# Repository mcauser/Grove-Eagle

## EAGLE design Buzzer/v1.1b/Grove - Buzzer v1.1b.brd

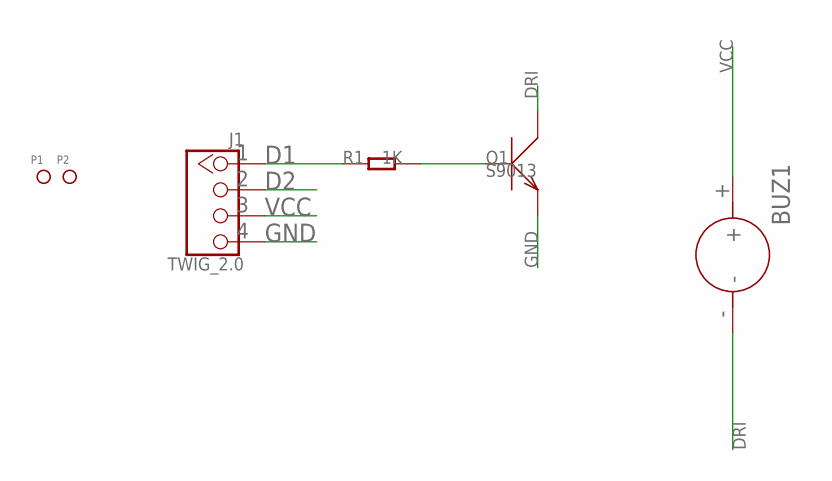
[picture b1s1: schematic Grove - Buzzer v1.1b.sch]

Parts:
BUZ1: BUZZER-YMD12065; 2P-7.6-D12X6.5H
J1: TWIG_2.0; 2.0_1X4
P1, P2: PAD-MARK; ROUND-MARK-1.0
Q1: S9013; SOT23
R1: 1K; R0603

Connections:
D1: J1.1, R1.1
D2: J1.2
DRI: BUZ1.-, Q1.3 (C)
GND: J1.4, Q1.2 (E)
unnamed: Q1.1 (B), R1.2
VCC: BUZ1.+, J1.3

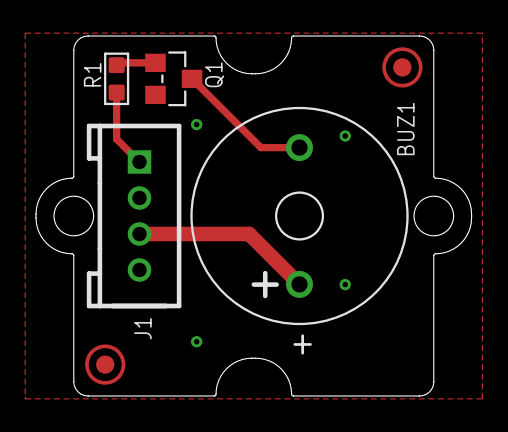
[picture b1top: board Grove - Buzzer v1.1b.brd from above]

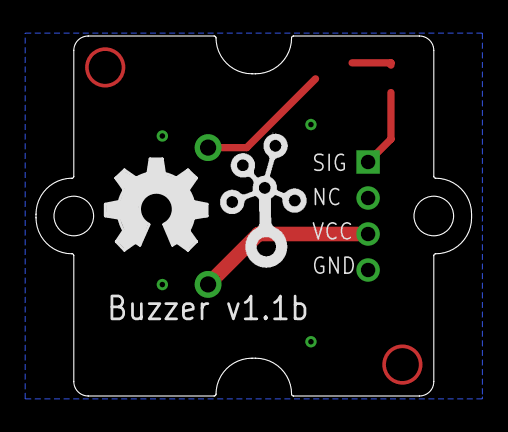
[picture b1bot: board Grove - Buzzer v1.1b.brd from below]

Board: 2 copper layers, 24.2 x 20.0 mm, 9 parts (2 on the bottom side), 5 nets.

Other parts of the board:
U$1: 1U-DIM-W/-DRILL
U$2: OSHW_FILLX200_NOTEXT
U$3: TWIGLOGO

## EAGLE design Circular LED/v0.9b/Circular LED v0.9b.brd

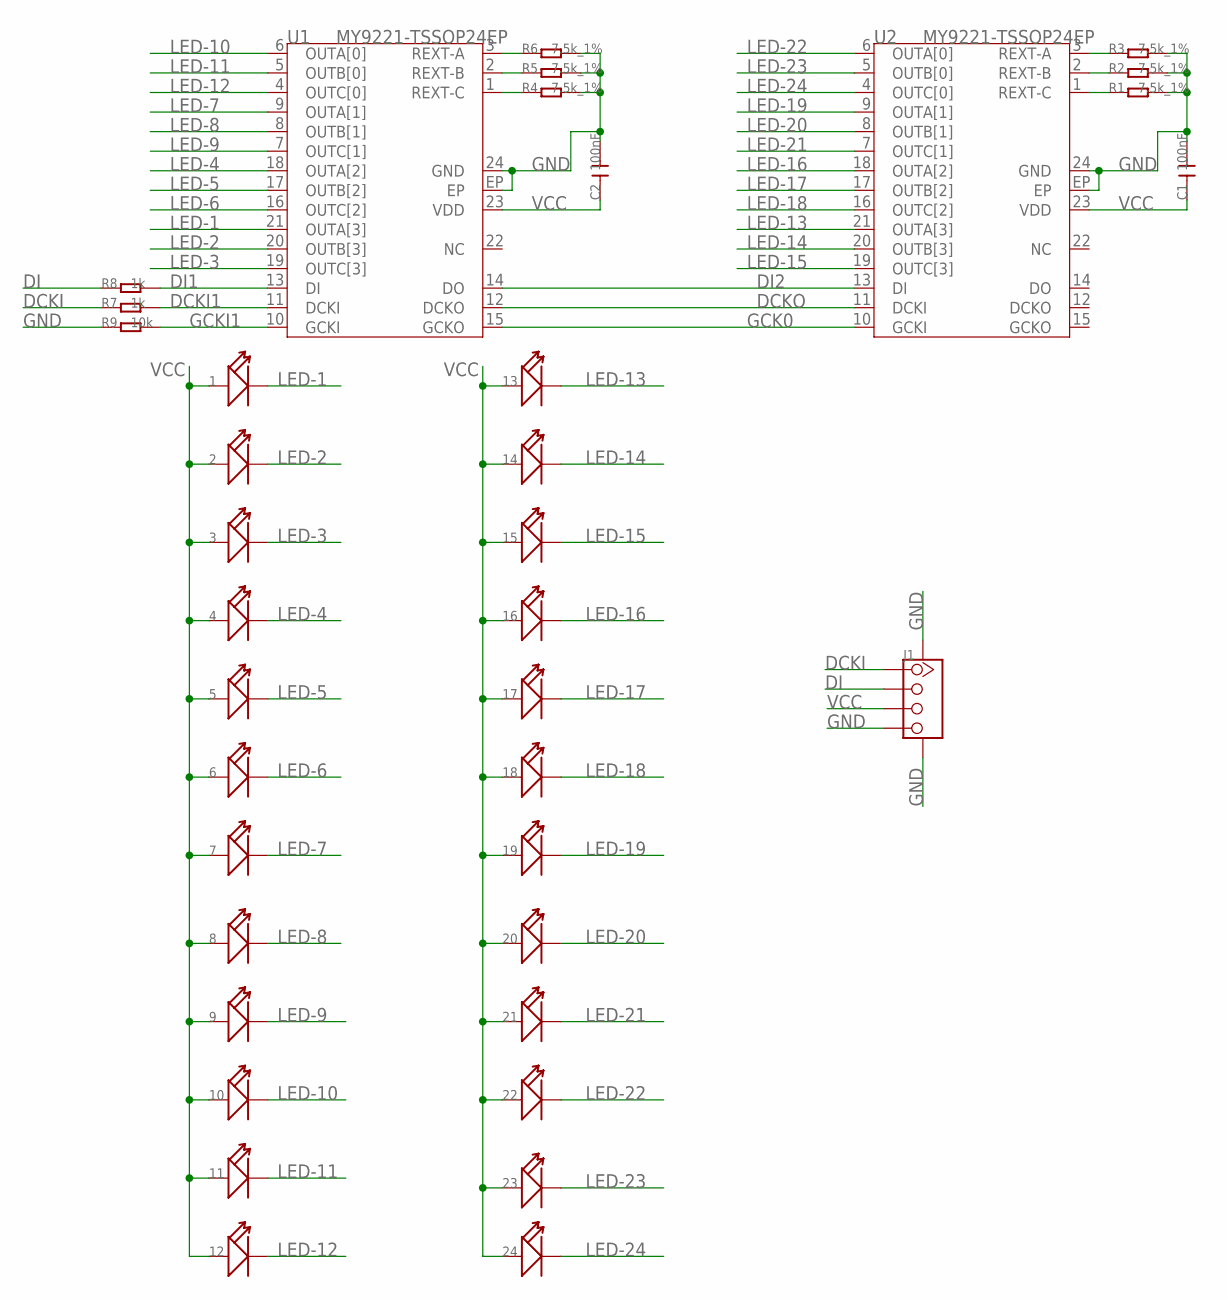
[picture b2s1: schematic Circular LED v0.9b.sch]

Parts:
1, 2, 3, 4, 5, 6, 7, 8, 9, 10, 11, 12, 13, 14, 15, 16, 17, 18, 19, 20, 21, 22, 23, 24: LED'1206'; LED-1206
C1, C2: 100nF; C0603
J1: TWIG-4P-2.0-SMD-FEMALE-REINFORCE'90D'; 4P-SMD-2.0-90D
R1, R2, R3, R4, R5, R6: 7.5k_1%; R0603
R7, R8: 1k; R0603
R9: 10k; R0603
U1, U2: MY9221-TSSOP24EP; TSSOP24EP

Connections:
DCKI: J1.1, R7.1
DCKI1: R7.2, U1.11 (DCKI)
DCKO: U1.12 (DCKO), U2.11 (DCKI)
DI: J1.2, R8.1
DI1: R8.2, U1.13 (DI)
DI2: U1.14 (DO), U2.13 (DI)
GCK0: U1.15 (GCKO), U2.10 (GCKI)
GCKI1: R9.2, U1.10 (GCKI)
GND: C1.2, C2.2, J1.4, J1.SS1, J1.SS2, R1.2, R2.2, R3.2, R4.2, R5.2, R6.2, R9.1, U1.24 (GND), U1.EP, U2.24 (GND), U2.EP
LED-1: 1.-, U1.21 (OUTA[3])
LED-2: 2.-, U1.20 (OUTB[3])
LED-3: 3.-, U1.19 (OUTC[3])
LED-4: 4.-, U1.18 (OUTA[2])
LED-5: 5.-, U1.17 (OUTB[2])
LED-6: 6.-, U1.16 (OUTC[2])
LED-7: 7.-, U1.9 (OUTA[1])
LED-8: 8.-, U1.8 (OUTB[1])
LED-9: 9.-, U1.7 (OUTC[1])
LED-10: 10.-, U1.6 (OUTA[0])
LED-11: 11.-, U1.5 (OUTB[0])
LED-12: 12.-, U1.4 (OUTC[0])
LED-13: 13.-, U2.21 (OUTA[3])
LED-14: 14.-, U2.20 (OUTB[3])
LED-15: 15.-, U2.19 (OUTC[3])
LED-16: 16.-, U2.18 (OUTA[2])
LED-17: 17.-, U2.17 (OUTB[2])
LED-18: 18.-, U2.16 (OUTC[2])
LED-19: 19.-, U2.9 (OUTA[1])
LED-20: 20.-, U2.8 (OUTB[1])
LED-21: 21.-, U2.7 (OUTC[1])
LED-22: 22.-, U2.6 (OUTA[0])
LED-23: 23.-, U2.5 (OUTB[0])
LED-24: 24.-, U2.4 (OUTC[0])
unnamed: R1.1, U2.1 (REXT-C)
unnamed: R2.1, U2.2 (REXT-B)
unnamed: R4.1, U1.1 (REXT-C)
unnamed: R5.1, U1.2 (REXT-B)
unnamed: R6.1, U1.3 (REXT-A)
unnamed: R3.1, U2.3 (REXT-A)
VCC: 1.+, 2.+, 3.+, 4.+, 5.+, 6.+, 7.+, 8.+, 9.+, 10.+, 11.+, 12.+, 13.+, 14.+, 15.+, 16.+, 17.+, 18.+, 19.+, 20.+, 21.+, 22.+, 23.+, 24.+, C1.1, C2.1, J1.3, U1.23 (VDD), U2.23 (VDD)

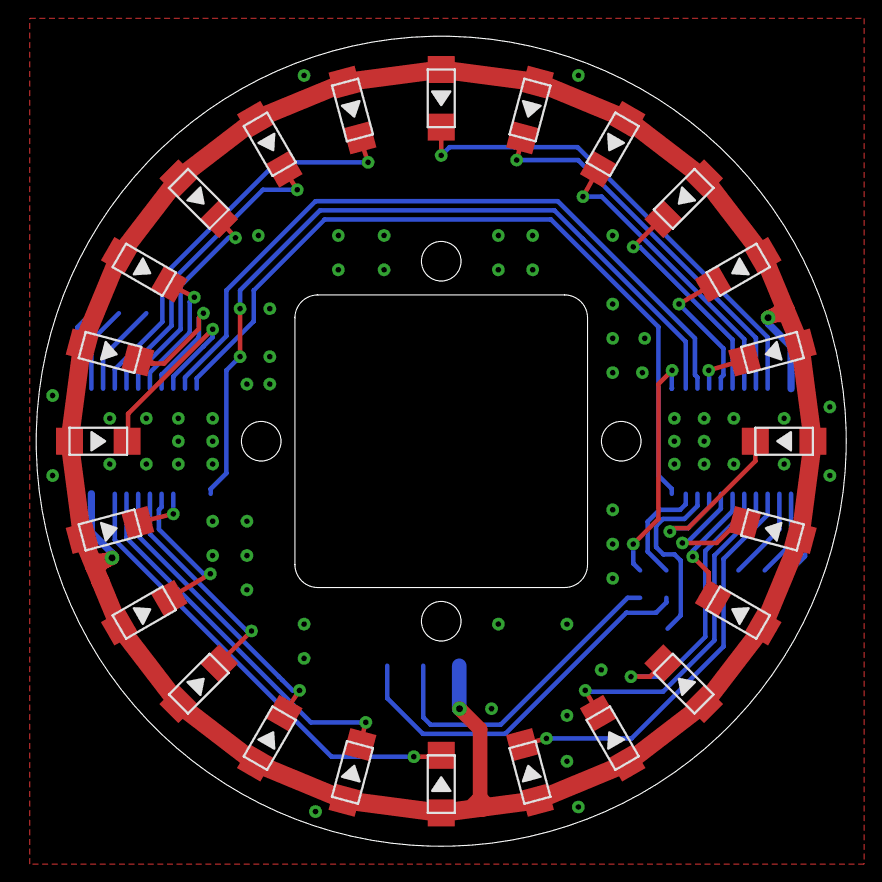
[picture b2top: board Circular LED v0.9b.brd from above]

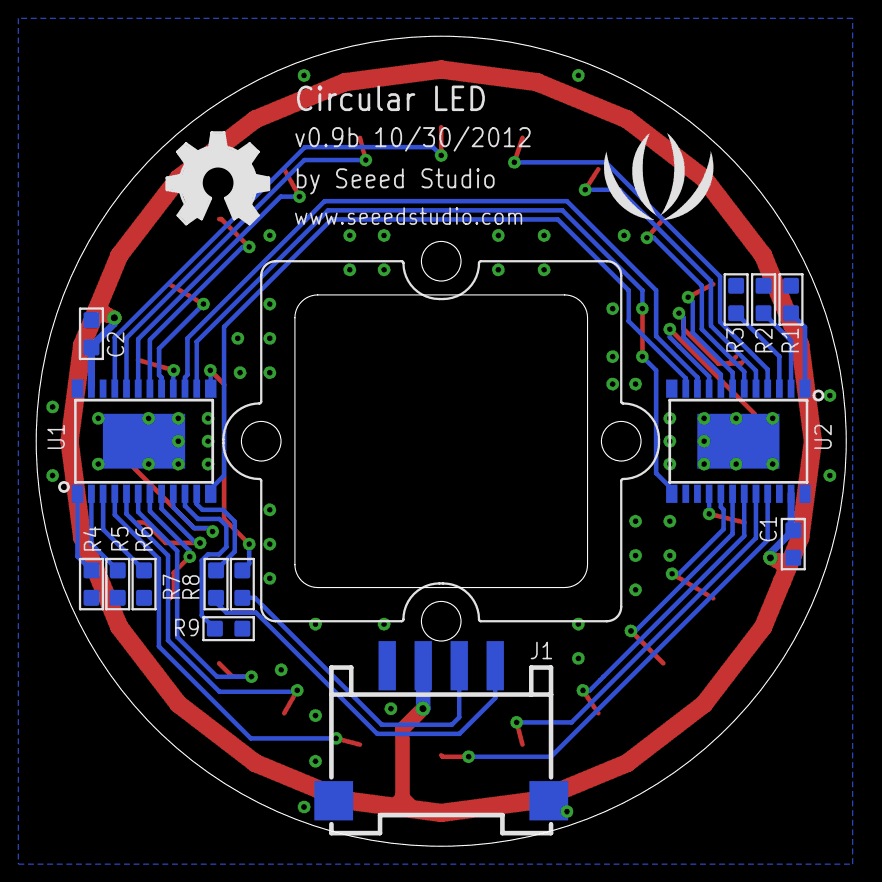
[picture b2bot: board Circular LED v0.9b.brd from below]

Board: 2 copper layers, 45.0 x 45.0 mm, 41 parts (17 on the bottom side), 40 nets.

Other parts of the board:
U$2: 1U-DIM-W/-DRILL-SILK
U$3: LOGO_SILK
U$4: OSHW_FILLX200_NOTEXT

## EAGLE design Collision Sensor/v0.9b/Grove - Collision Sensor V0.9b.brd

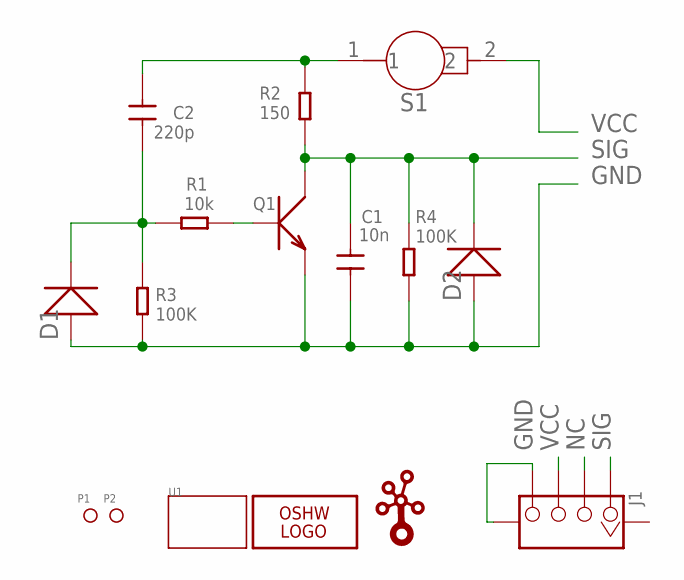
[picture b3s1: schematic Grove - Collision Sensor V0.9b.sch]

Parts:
C1: 10n; 0603
C2: 220p; 0603
D1, D2: D1N4148-SMD; DO-35-SMD
J1: TWIG-4P-2.0-SMD-FEMALE-REINFORCE'DD'; 4P-SMD-2.0
LOGO1: LOGO-OSHW-6MILX0200-NT; OSHW_6X200_NOTEXT
P1, P2: PAD-MARK; ROUND-MARK-0.635
Q1: TRANSISTOR-NPN-SOT23''; SOT23
R1: 10k; 0603
R2: 150; 0603
R3, R4: 100K; 0603
S1: SENSOR-COLLISION; 2P-ROUND-D5.4MM
U1: TWIG-1U; 1U-DIM-W/-DRILL
U$2: LOGO-TWIG; TWIGLOGO

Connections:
GND: C1.1, D1.A (+), D2.A (+), J1.4, J1.SS2, Q1.2 (E), R3.2, R4.2
unnamed: C2.2, R2.1, S1.1
unnamed: C2.1, D1.C (-), R1.2, R3.1
unnamed: Q1.1 (B), R1.1
NC: J1.2
SIG: C1.2, D2.C (-), J1.1, Q1.3 (C), R2.2, R4.1
VCC: J1.3, S1.2

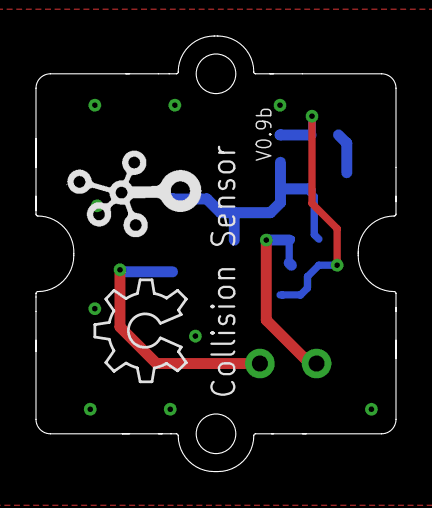
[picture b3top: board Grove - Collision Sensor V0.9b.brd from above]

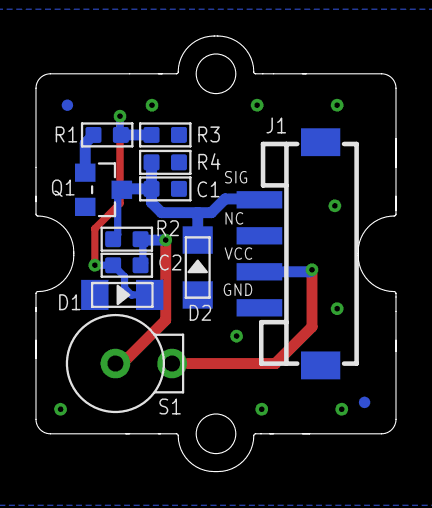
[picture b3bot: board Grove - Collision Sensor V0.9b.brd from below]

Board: 2 copper layers, 20.0 x 24.2 mm, 16 parts (14 on the bottom side), 6 nets.

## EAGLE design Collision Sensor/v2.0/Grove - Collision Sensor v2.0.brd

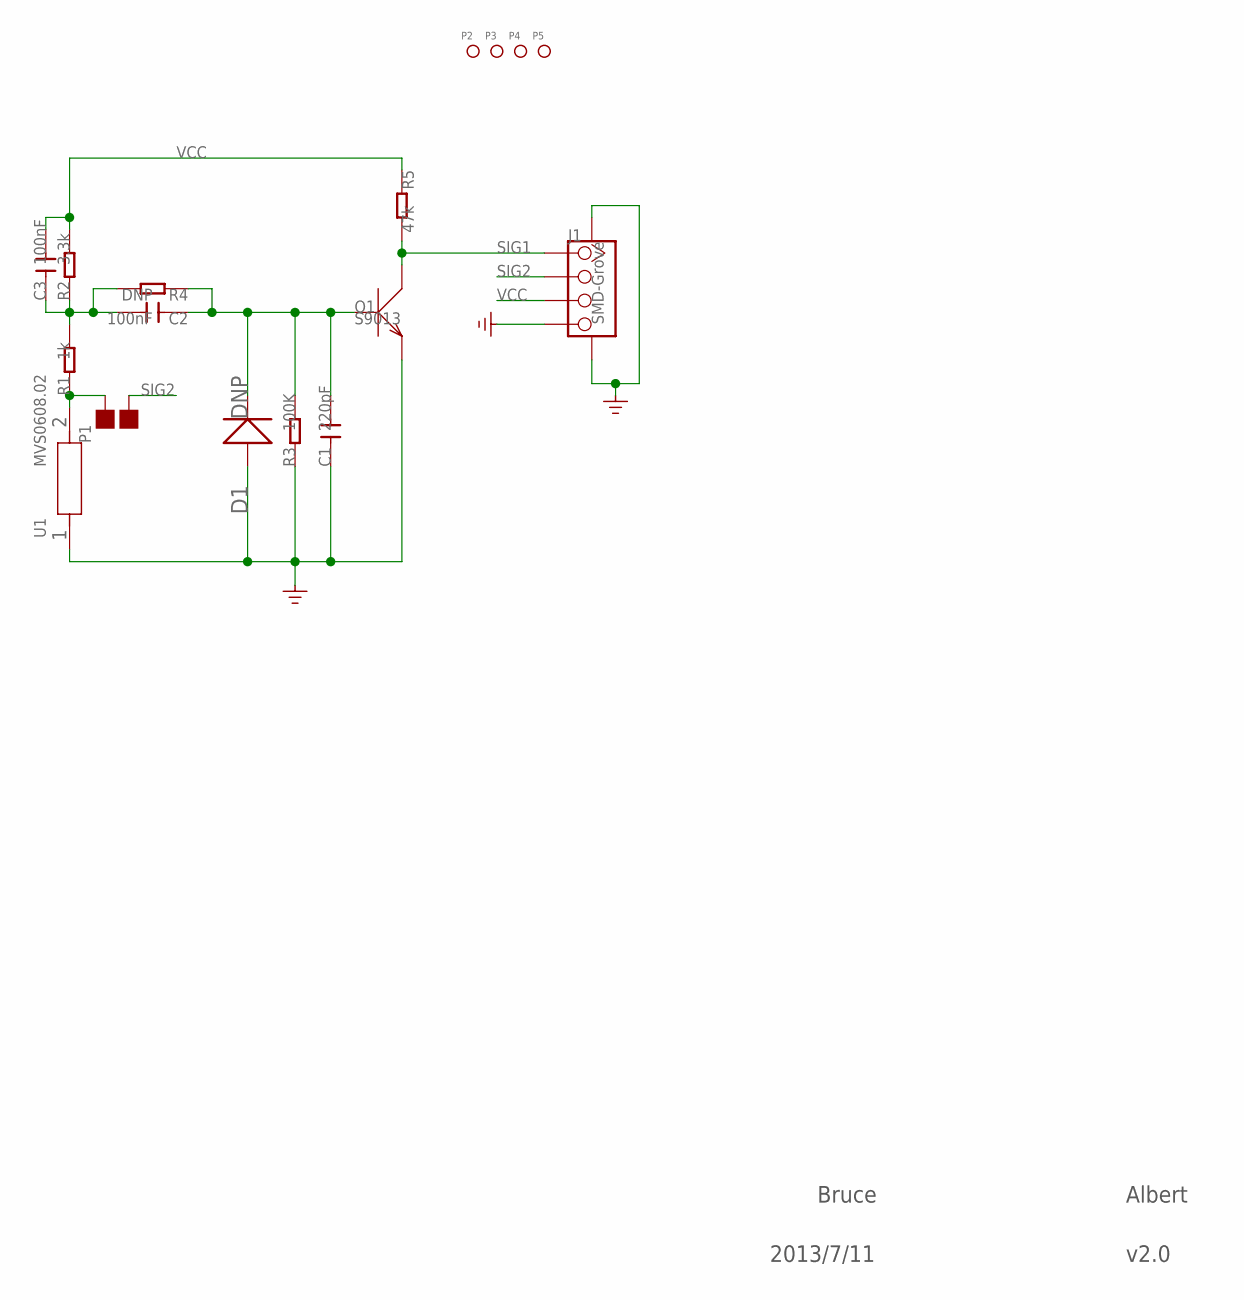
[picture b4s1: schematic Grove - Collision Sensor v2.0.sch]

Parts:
C1: 220pF; C0603
C2, C3: 100nF; C0603
D1: DNP; SOD123
J1: SMD-Grove; 4P-SMD-2.0
P1: DNP; 2P-SMD-1.78X1.27
P2, P3, P4, P5: PAD-MARK; ROUND-MARK-1.0
Q1: S9013; SOT23
R1: 1k; R0603
R2: 3.3k; R0603
R3: 100K; R0603
R4: DNP; R0603
R5: 47k; R0603
U1: MVS0608.02; 2P-2.45X2.85X1.7H

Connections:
GND: C1.1, D1.+, J1.4, J1.SS1, J1.SS2, Q1.2 (E), R3.1, U1.1
unnamed: P1.2, R1.1, U1.2
unnamed: C2.2, C3.1, R1.2, R2.1, R4.2
unnamed: C1.2, C2.1, D1.-, Q1.1 (B), R3.2, R4.1
SIG1: J1.1, Q1.3 (C), R5.2
SIG2: J1.2, P1.1
VCC: C3.2, J1.3, R2.2, R5.1

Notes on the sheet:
Bruce
Albert
2013/7/11
v2.0

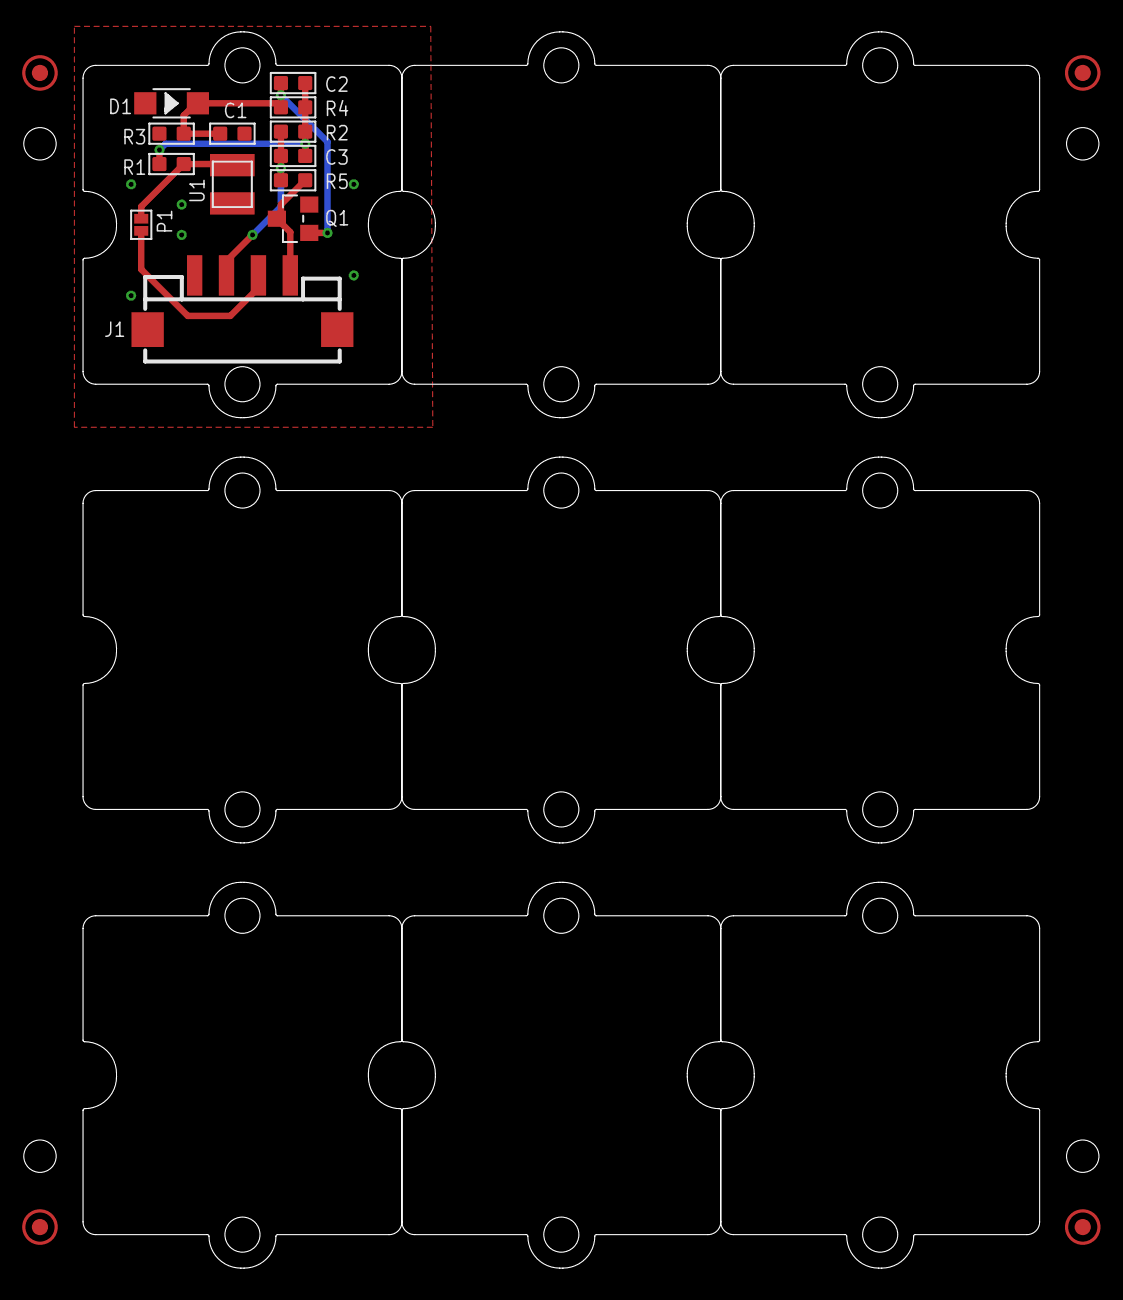
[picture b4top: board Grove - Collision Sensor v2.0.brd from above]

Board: 2 copper layers, 60.0 x 77.5 mm, 28 parts (2 on the bottom side), 7 nets.

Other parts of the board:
U$5: OSHW_FILLX200_NOTEXT
U$6, U$8, U$9, U$10, U$11, U$12, U$13, U$14, U$15: 1U-DIM-W/-DRILL
U$7: TWIGLOGO
